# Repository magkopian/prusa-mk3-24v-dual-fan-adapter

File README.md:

Dual 24V Fan Adapter for the Original Prusa i3 MK3
================================

## Description:

This is an adapter board that allows you to easily connect two 24V fans on an Original Prusa i3 MK3 in place of the stock 5V fan. This repository contains the source design files, as well as [gerber files](/gerbers) for easily ordering PCBs from the PCB manufacturer of your choice.

## How to install:

The two 24V fans are being attached on the board via screw terminals. Then, the adapter board connects directly to the fan connector of the Einsy Rambo and receives 24V via pin 1 of the J19 header (also known as the Pi Port), using a male to female jumper wire. It's recommended to use 45° screw terminals as they need to be facing inwards, due to the fact that fuse `F3` on the Einsy is on the way and there is no room to attach the wires if the screw terminals are facing the other way. I also recommend terminating your fan wires using ferrules for ensuring a sold connection.

The board features an optional connection for a tacho signal from a 3-pin fan, which in order to be used the pin on the fan must be an open collector type. Most 3-wire fans should use an open collector tacho signal but this not guaranteed, so make sure to check your fan or you might damage your controller board if that is not the case. If you want to use two 3-pin fans use the tacho signal only from one of them, do not connect the two wires in parallel.

If you don't have a 3-pin 24V fan or you don't want to use the tacho signal connection for whatever reason, you will have to disable the `fans check` from the printer menu or you're going to get a fan error. Unfortunately, at the time of the writing there is no way of disabling the check just for the layer fan, so turning off the `fans check` means that the heatsink fan will neither be monitored any longer. It's up to you to decide whether you are fine with taking that risk, in my case this is what I did as I don't have a 3-pin 24V.

## License:

The design files for the PCB are distributed under the [Attribution-ShareAlike 4.0 International](https://creativecommons.org/licenses/by-sa/4.0/) license.

## Disclaimer:

**Use this at your own risk. I am not held responsible for any damage you might cause to your printer.**

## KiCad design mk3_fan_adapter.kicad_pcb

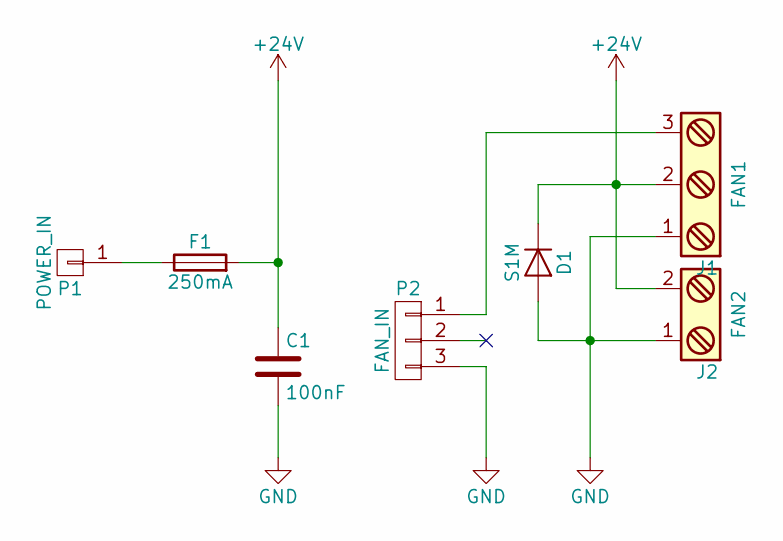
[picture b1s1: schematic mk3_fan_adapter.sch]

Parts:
C1: 100nF; C_0603
D1: S1M; D_SMA
F1: 250mA; Fuse_CB61F
J1: FAN1; TerminalBlock_Pheonix_PT-3.5mm_3pol
J2: FAN2; TerminalBlock_Pheonix_PT-3.5mm_2pol
P1: POWER_IN; Pin_Header_Angled_1x01_Pitch2.54mm
P2: FAN_IN; Pin_Header_Straight_1x03_Pitch2.54mm

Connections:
+24V: C1.1, D1.1 (K), F1.2, J1.2, J2.2
GND: C1.2, D1.2 (A), J1.1, J2.1, P2.3
unnamed: F1.1, P1.1
unnamed: J1.3, P2.1

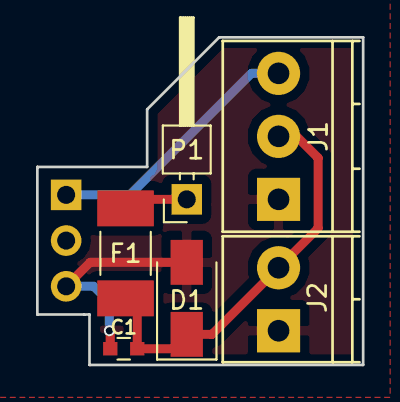
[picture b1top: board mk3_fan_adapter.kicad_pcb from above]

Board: 2 copper layers, 18.1 x 18.2 mm, 7 parts (1 on the bottom side), 4 nets.

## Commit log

2018-08-28 Added README
2019-01-31 Added board image
